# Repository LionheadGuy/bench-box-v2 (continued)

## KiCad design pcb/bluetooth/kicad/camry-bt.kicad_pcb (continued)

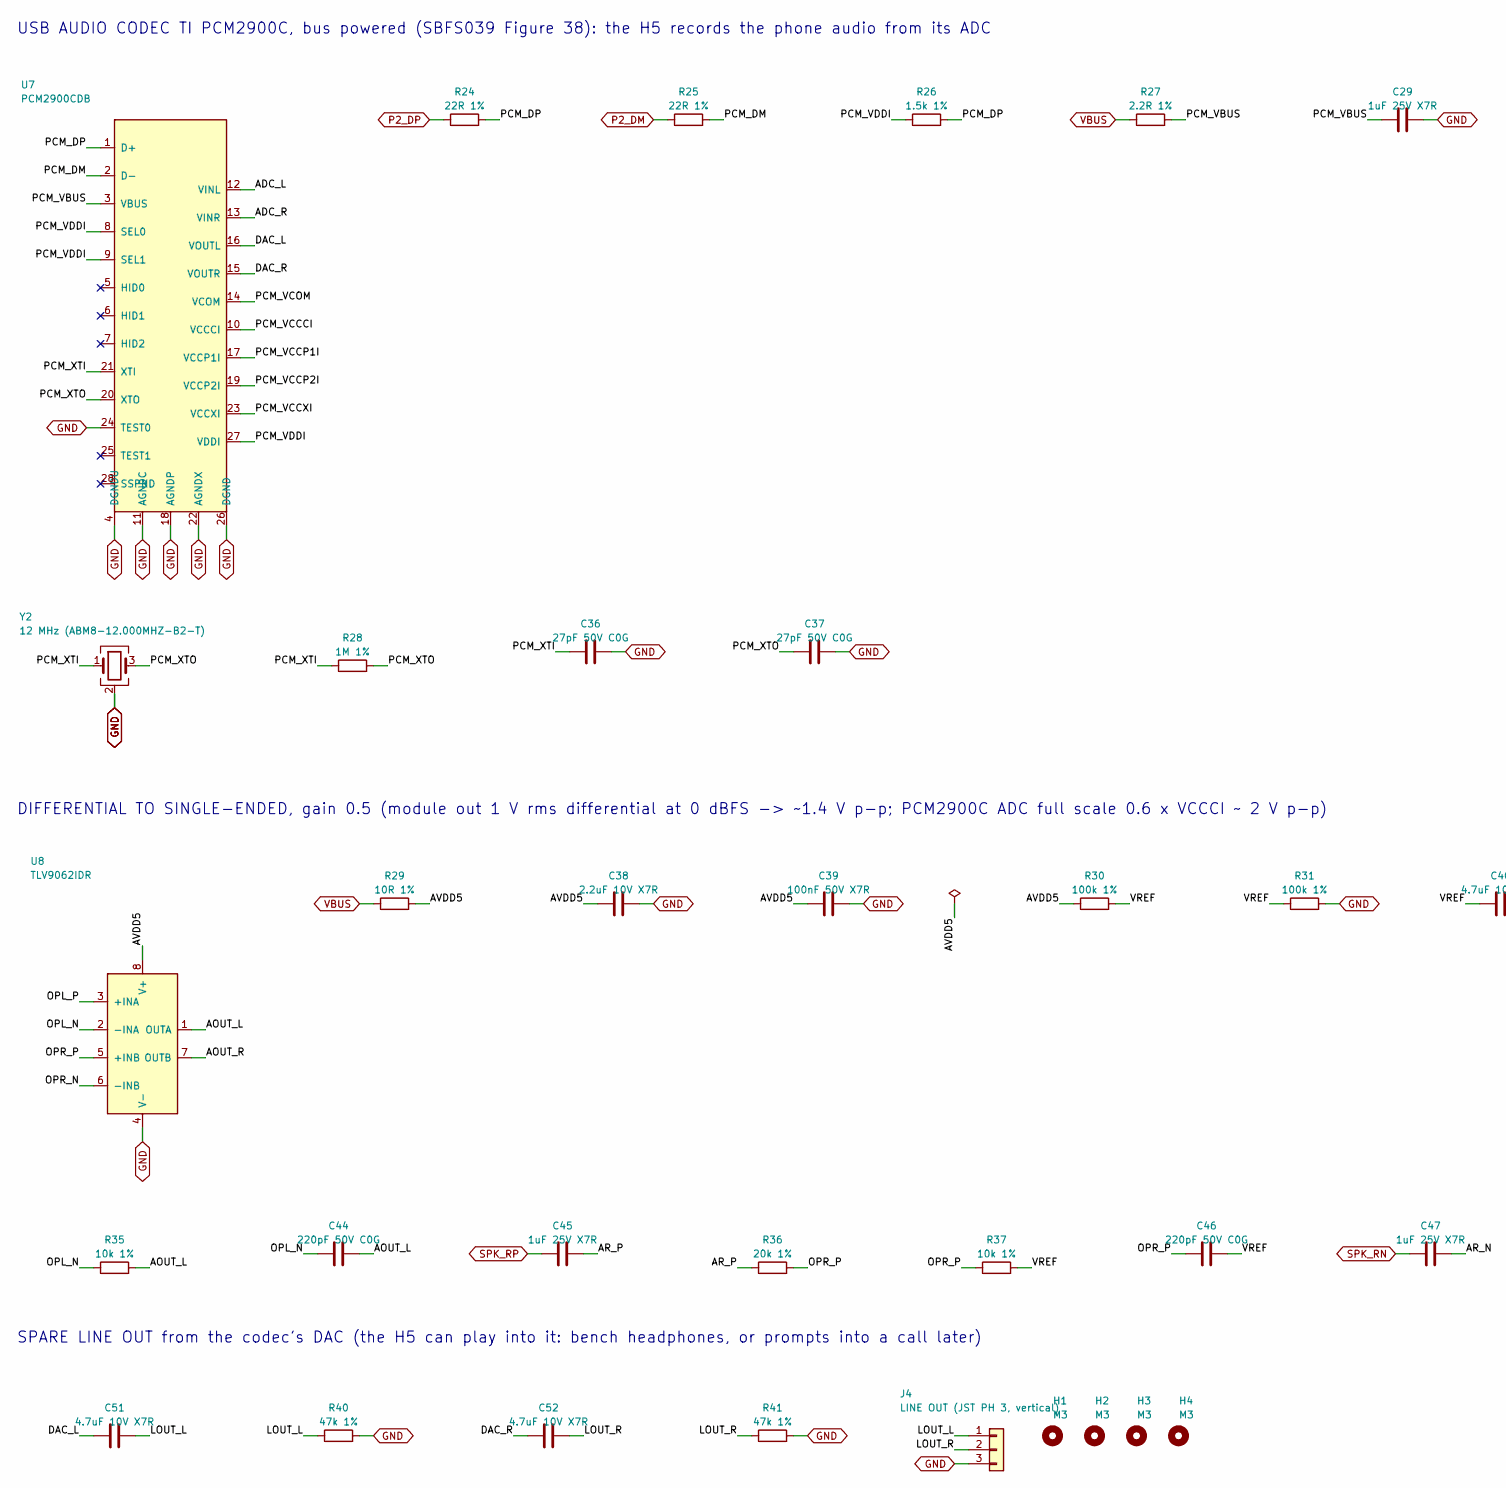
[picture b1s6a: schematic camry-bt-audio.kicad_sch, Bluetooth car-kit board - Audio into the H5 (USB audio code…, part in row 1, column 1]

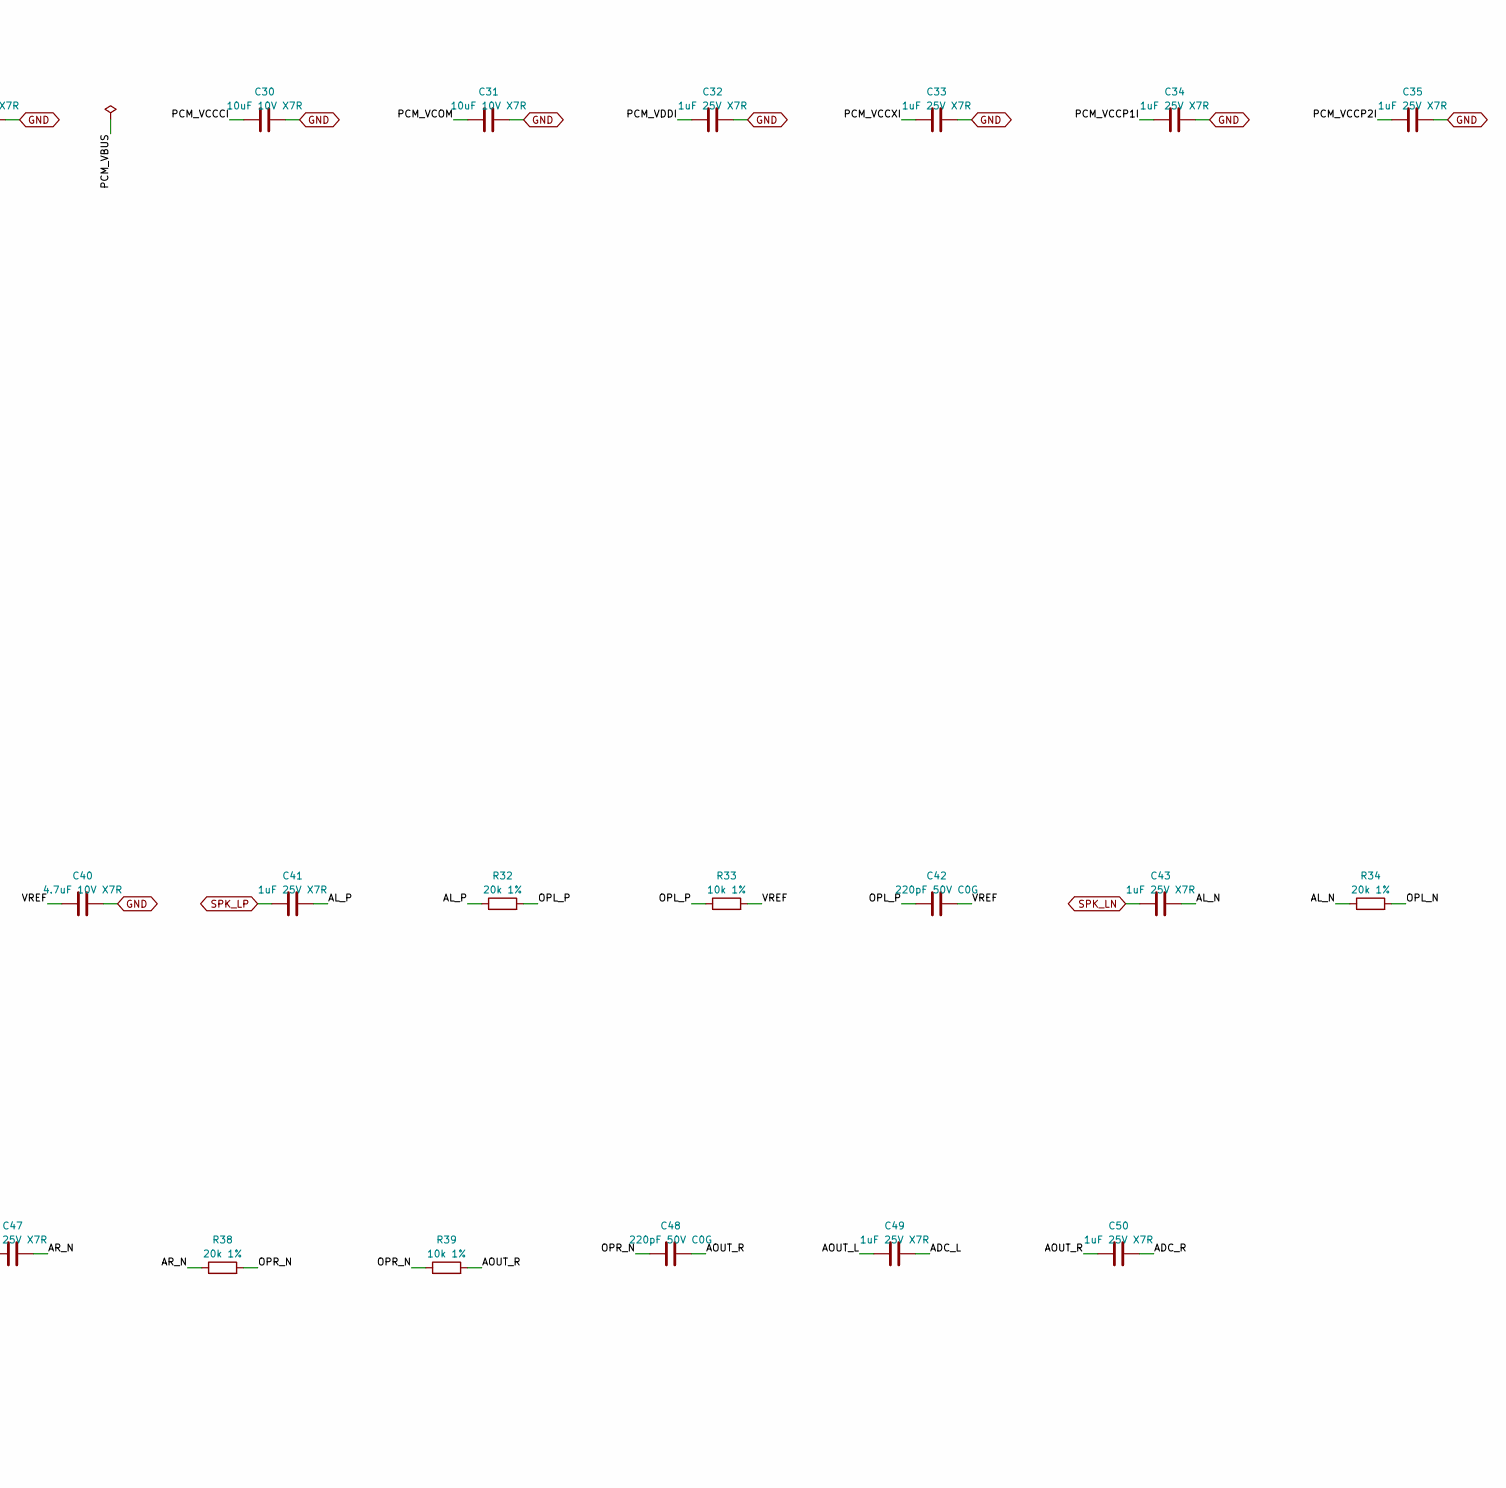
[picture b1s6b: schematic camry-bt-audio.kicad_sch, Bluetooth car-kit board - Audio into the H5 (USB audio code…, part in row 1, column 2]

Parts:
C29, C32, C33, C34, C35, C41, C43, C45, C47, C49, C50: 1uF 25V X7R; C_0603_1608Metric; MPN GRM188R71E105KA12D
C30, C31: 10uF 10V X7R; C_0805_2012Metric; MPN GRM21BR71A106KA73L
C36, C37: 27pF 50V C0G; C_0603_1608Metric; MPN GRM1885C1H270JA01D
C38: 2.2uF 10V X7R; C_0603_1608Metric; MPN GRM188R71A225KE15D
C39: 100nF 50V X7R; C_0603_1608Metric; MPN GRM188R71H104KA93D
C40, C51, C52: 4.7uF 10V X7R; C_0805_2012Metric; MPN GRM21BR71A475KA73L
C42, C44, C46, C48: 220pF 50V C0G; C_0603_1608Metric; MPN GRM1885C1H221JA01D
H1, H2, H3, H4: M3; MountingHole_3.2mm_M3
J4: LINE OUT (JST PH 3, vertical); JST_PH_B3B-PH-K_1x03_P2.00mm_Vertical; MPN B3B-PH-K-S(LF)(SN)
R24, R25: 22R 1%; R_0402_1005Metric; MPN RC0402FR-0722RL
R26: 1.5k 1%; R_0402_1005Metric; MPN RC0402FR-071K5L
R27: 2.2R 1%; R_0402_1005Metric; MPN RC0402FR-072R2L
R28: 1M 1%; R_0402_1005Metric; MPN RC0402FR-071ML
R29: 10R 1%; R_0402_1005Metric; MPN RC0402FR-0710RL
R30, R31: 100k 1%; R_0402_1005Metric; MPN RC0402FR-07100KL
R32, R34, R36, R38: 20k 1%; R_0402_1005Metric; MPN RC0402FR-0720KL
R33, R35, R37, R39: 10k 1%; R_0402_1005Metric; MPN RC0402FR-0710KL
R40, R41: 47k 1%; R_0402_1005Metric; MPN RC0402FR-0747KL
U7: PCM2900CDB; SSOP-28_5.3x10.2mm_P0.65mm; MPN PCM2900CDB
U8: TLV9062IDR; SOIC-8_3.9x4.9mm_P1.27mm; MPN TLV9062IDR
Y2: 12 MHz (ABM8-12.000MHZ-B2-T); Crystal_SMD_3225-4Pin_3.2x2.5mm; MPN ABM8-12.000MHZ-B2-T

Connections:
/Audio into the H5 (USB audio codec)/ADC_L: C49.2, U7.12 (VINL)
/Audio into the H5 (USB audio codec)/ADC_R: C50.2, U7.13 (VINR)
/Audio into the H5 (USB audio codec)/AL_N: C43.2, R34.1
/Audio into the H5 (USB audio codec)/AL_P: C41.2, R32.1
/Audio into the H5 (USB audio codec)/AOUT_L: C44.2, C49.1, R35.2, U8.1 (OUTA)
/Audio into the H5 (USB audio codec)/AOUT_R: C48.2, C50.1, R39.2, U8.7 (OUTB)
/Audio into the H5 (USB audio codec)/AR_N: C47.2, R38.1
/Audio into the H5 (USB audio codec)/AR_P: C45.2, R36.1
/Audio into the H5 (USB audio codec)/AVDD5: C38.1, C39.1, R29.2, R30.1, U8.8 (V+)
/Audio into the H5 (USB audio codec)/DAC_L: C51.1, U7.16 (VOUTL)
/Audio into the H5 (USB audio codec)/DAC_R: C52.1, U7.15 (VOUTR)
/Audio into the H5 (USB audio codec)/LOUT_L: C51.2, J4.1, R40.1
/Audio into the H5 (USB audio codec)/LOUT_R: C52.2, J4.2, R41.1
/Audio into the H5 (USB audio codec)/OPL_N: C44.1, R34.2, R35.1, U8.2 (-INA)
/Audio into the H5 (USB audio codec)/OPL_P: C42.1, R32.2, R33.1, U8.3 (+INA)
/Audio into the H5 (USB audio codec)/OPR_N: C48.1, R38.2, R39.1, U8.6 (-INB)
/Audio into the H5 (USB audio codec)/OPR_P: C46.1, R36.2, R37.1, U8.5 (+INB)
/Audio into the H5 (USB audio codec)/PCM_DM: R25.2, U7.2 (D-)
/Audio into the H5 (USB audio codec)/PCM_DP: R24.2, R26.2, U7.1 (D+)
/Audio into the H5 (USB audio codec)/PCM_VBUS: C29.1, R27.2, U7.3 (VBUS)
/Audio into the H5 (USB audio codec)/PCM_VCCCI: C30.1, U7.10 (VCCCI)
/Audio into the H5 (USB audio codec)/PCM_VCCP1I: C34.1, U7.17 (VCCP1I)
/Audio into the H5 (USB audio codec)/PCM_VCCP2I: C35.1, U7.19 (VCCP2I)
/Audio into the H5 (USB audio codec)/PCM_VCCXI: C33.1, U7.23 (VCCXI)
/Audio into the H5 (USB audio codec)/PCM_VCOM: C31.1, U7.14 (VCOM)
/Audio into the H5 (USB audio codec)/PCM_VDDI: C32.1, R26.1, U7.8 (SEL0), U7.9 (SEL1), U7.27 (VDDI)
/Audio into the H5 (USB audio codec)/PCM_XTI: C36.1, R28.1, U7.21 (XTI), Y2.1
/Audio into the H5 (USB audio codec)/PCM_XTO: C37.1, R28.2, U7.20 (XTO), Y2.3
/Audio into the H5 (USB audio codec)/VREF: C40.1, C42.2, C46.2, R30.2, R31.1, R33.2, R37.2
GND: C29.2, C30.2, C31.2, C32.2, C33.2, C34.2, C35.2, C36.2, C37.2, C38.2, C39.2, C40.2, J4.3, R31.2, R40.2, R41.2, U7.4 (DGNDU), U7.11 (AGNDC), U7.18 (AGNDP), U7.22 (AGNDX), U7.24 (TEST0), U7.26 (DGND), U8.4 (V-), Y2.2 (G), Y2.4 (G); also elsewhere on the board
P2_DM: R25.1; also elsewhere on the board
P2_DP: R24.1; also elsewhere on the board
SPK_LN: C43.1; also elsewhere on the board
SPK_LP: C41.1; also elsewhere on the board
SPK_RN: C47.1; also elsewhere on the board
SPK_RP: C45.1; also elsewhere on the board
VBUS: R27.1, R29.1; also elsewhere on the board

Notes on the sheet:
USB AUDIO CODEC TI PCM2900C, bus powered (SBFS039 Figure 38): the H5 records the phone audio from its ADC
DIFFERENTIAL TO SINGLE-ENDED, gain 0.5 (module out 1 V rms differential at 0 dBFS -> ~1.4 V p-p; PCM2900C ADC full scale 0.6 x VCCCI ~ 2 V p-p)
SPARE LINE OUT from the codec's DAC (the H5 can play into it: bench headphones, or prompts into a call later)

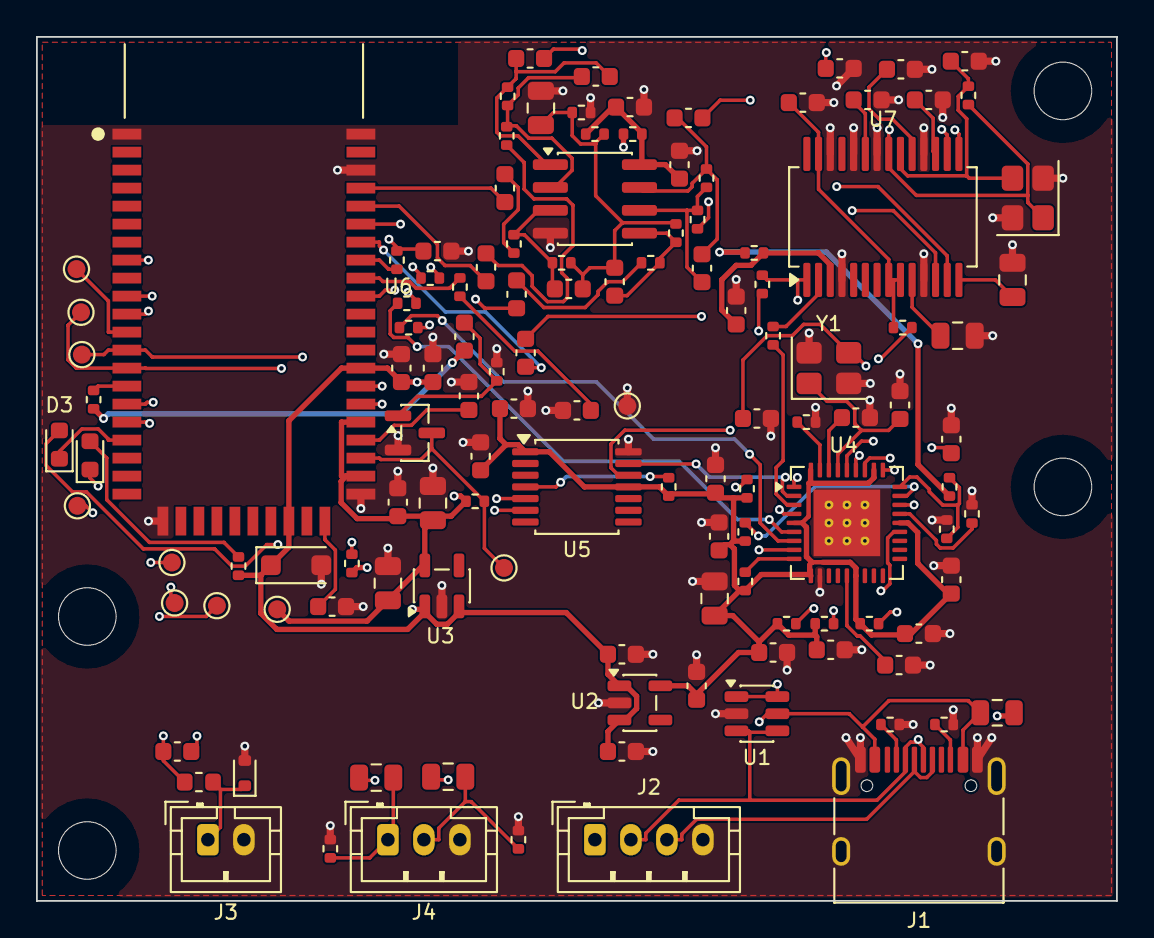
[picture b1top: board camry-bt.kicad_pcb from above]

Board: 4 copper layers, 60.0 x 48.0 mm, 128 parts (0 on the bottom side), 87 nets.

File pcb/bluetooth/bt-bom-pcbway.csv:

Item,Qty,Designators,Manufacturer,MPN,LCSC,Description,Footprint,Type,Substitute
1,1,U1,STMicroelectronics,USBLC6-2SC6,,"USB ESD protection, SOT-23-6",SOT-23-6,SMD,exact part only
2,2,U2 U3,Texas Instruments,TLV75533PDBVR,,"LDO 3.3 V 500 mA, SOT-23-5",SOT-23-5,SMD,exact part only
3,1,U4,Microchip,USB2514BI-AEZG,,"USB 2.0 4-port hub, QFN-36 6x6, -40 to 85 C",QFN-36-1EP_6x6mm_P0.5mm_EP3.7x3.7mm_ThermalVias,SMD,exact part only
4,1,U5,Microchip,MCP2221A-I/ST,,"USB to UART/I2C, TSSOP-14",TSSOP-14_4.4x5mm_P0.65mm,SMD,exact part only
5,1,U6,Feasycom,FSC-BT1026C,,"Bluetooth 5.1 audio module QCC3024, 52-pad stamp 13 x 26.9 mm (DigiKey stocks it)",Feasycom_FSC-BT1026x,SMD,exact part only
6,1,U7,Texas Instruments,PCM2900CDB,,"USB stereo audio codec, SSOP-28",SSOP-28_5.3x10.2mm_P0.65mm,SMD,exact part only
7,1,U8,Texas Instruments,TLV9062IDR,,"dual RRIO op amp 1.8-5.5 V, SOIC-8",SOIC-8_3.9x4.9mm_P1.27mm,SMD,exact part only
8,1,Q1,onsemi,2N7002LT1G,,"N-MOSFET 60 V 115 mA, SOT-23",SOT-23,SMD,exact part only
9,1,L1,Murata,LQG18HN15NJ00D,,"inductor 15 nH, 0603",L_0603_1608Metric,SMD,exact part only
10,1,D1,Littelfuse,SMF5.0A,,"TVS 5 V standoff, SOD-123FL",D_SOD-123F,SMD,exact part only
11,1,D2,Lite-On,LTST-C191TBKT,,"LED blue, 0603",LED_0603_1608Metric,SMD,exact part only
12,1,D3,Lite-On,LTST-C191KGKT,,"LED green, 0603",LED_0603_1608Metric,SMD,exact part only
13,1,D4,onsemi,ESD5Z5.0T1G,,"ESD diode 5 V, SOD-523",D_SOD-523,SMD,exact part only
14,1,Y1,Abracon,ABM8-24.000MHZ-B2-T,,"crystal 24 MHz, 18 pF, 3.2 x 2.5 mm",Crystal_SMD_3225-4Pin_3.2x2.5mm,SMD,exact part only
15,1,Y2,Abracon,ABM8-12.000MHZ-B2-T,,"crystal 12 MHz, 18 pF, 3.2 x 2.5 mm",Crystal_SMD_3225-4Pin_3.2x2.5mm,SMD,exact part only
16,1,F1,Bourns,MF-PSMF050X-2,,"PTC resettable fuse 0.5 A hold, 0805",Fuse_0805_2012Metric,SMD,exact part only
17,1,J1,Korean Hroparts Elec (HRO),TYPE-C-31-M-12,C165948,USB-C receptacle 16P,USB_C_Receptacle_HRO_TYPE-C-31-M-12,SMD,exact part only
18,1,J2,JST,B4B-PH-K-S(LF)(SN),,JST PH 4-pin vertical header,JST_PH_B4B-PH-K_1x04_P2.00mm_Vertical,THT,exact part only
19,1,J3,JST,B2B-PH-K-S(LF)(SN),,JST PH 2-pin vertical header,JST_PH_B2B-PH-K_1x02_P2.00mm_Vertical,THT,exact part only
20,1,J4,JST,B3B-PH-K-S(LF)(SN),,JST PH 3-pin vertical header,JST_PH_B3B-PH-K_1x03_P2.00mm_Vertical,THT,exact part only
21,3,C1 C23 C38,Murata,GRM188R71A225KE15D,,2.2 uF 10 V X7R 0603,C_0603_1608Metric,SMD,equivalent OK
22,4,C15 C16 C36 C37,Murata,GRM1885C1H270JA01D,,27 pF 50 V C0G 0603,C_0603_1608Metric,SMD,equivalent OK
23,1,C19,Murata,GRM188R71C474KA88D,,470 nF 16 V X7R 0603,C_0603_1608Metric,SMD,equivalent OK
24,18,C2 C3 C4 C17 C22 C24 C25 C29 C32 C33 C34 C35 C41 C43 C45 C47 C49 C50,Murata,GRM188R71E105KA12D,,1 uF 25 V X7R 0603,C_0603_1608Metric,SMD,equivalent OK
25,1,C26,Murata,GRM1885C1H150JA01D,,15 pF 50 V C0G 0603,C_0603_1608Metric,SMD,equivalent OK
26,2,C30 C31,Murata,GRM21BR71A106KA73L,,10 uF 10 V X7R 0805,C_0805_2012Metric,SMD,equivalent OK
27,4,C42 C44 C46 C48,Murata,GRM1885C1H221JA01D,,220 pF 50 V C0G 0603,C_0603_1608Metric,SMD,equivalent OK
28,6,C5 C12 C21 C40 C51 C52,Murata,GRM21BR71A475KA73L,,4.7 uF 10 V X7R 0805,C_0805_2012Metric,SMD,equivalent OK
29,13,C6 C7 C8 C9 C10 C11 C13 C14 C18 C20 C27 C28 C39,Murata,GRM188R71H104KA93D,,100 nF 50 V X7R 0603,C_0603_1608Metric,SMD,equivalent OK
30,2,R1 R2,Yageo,RC0402FR-075K1L,,5.1 k 1 % 0402,R_0402_1005Metric,SMD,equivalent OK
31,4,R14 R15 R24 R25,Yageo,RC0402FR-0722RL,,22 Ohm 1 % 0402,R_0402_1005Metric,SMD,equivalent OK
32,1,R18,Yageo,RC0402FR-072KL,,2 k 1 % 0402,R_0402_1005Metric,SMD,equivalent OK
33,4,R19 R20 R22 R23,Yageo,RC0402FR-071KL,,1 k 1 % 0402,R_0402_1005Metric,SMD,equivalent OK
34,1,R21,Yageo,RC0402FR-072K2L,,2.2 k 1 % 0402,R_0402_1005Metric,SMD,equivalent OK
35,1,R26,Yageo,RC0402FR-071K5L,,1.5 k 1 % 0402,R_0402_1005Metric,SMD,equivalent OK
36,1,R27,Yageo,RC0402FR-072R2L,,2.2 Ohm 1 % 0402,R_0402_1005Metric,SMD,equivalent OK
37,1,R28,Yageo,RC0402FR-071ML,,1 M 1 % 0402,R_0402_1005Metric,SMD,equivalent OK
38,1,R29,Yageo,RC0402FR-0710RL,,10 Ohm 1 % 0402,R_0402_1005Metric,SMD,equivalent OK
39,1,R3,Yageo,RC0402FR-0712KL,,12.0 k 1 % 0402,R_0402_1005Metric,SMD,equivalent OK
40,4,R32 R34 R36 R38,Yageo,RC0402FR-0720KL,,20 k 1 % 0402,R_0402_1005Metric,SMD,equivalent OK
41,11,R4 R7 R8 R11 R12 R13 R16 R33 R35 R37 R39,Yageo,RC0402FR-0710KL,,10 k 1 % 0402,R_0402_1005Metric,SMD,equivalent OK
42,2,R40 R41,Yageo,RC0402FR-0747KL,,47 k 1 % 0402,R_0402_1005Metric,SMD,equivalent OK
43,7,R5 R6 R9 R10 R17 R30 R31,Yageo,RC0402FR-07100KL,,100 k 1 % 0402,R_0402_1005Metric,SMD,equivalent OK

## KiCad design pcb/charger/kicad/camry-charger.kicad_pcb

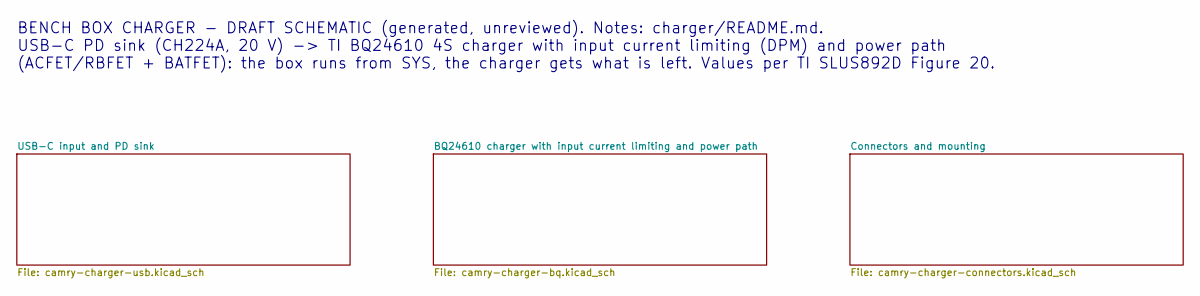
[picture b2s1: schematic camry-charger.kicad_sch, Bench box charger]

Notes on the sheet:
BENCH BOX CHARGER - DRAFT SCHEMATIC (generated, unreviewed). Notes: charger/README.md. USB-C PD sink (CH224A, 20 V) -> TI BQ24610 4S charger with input current limiting (DPM) and power path (ACFET/RBFET + BATFET): the box runs from SYS, the charger gets what is left. Values per TI SLUS892D Figure 2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

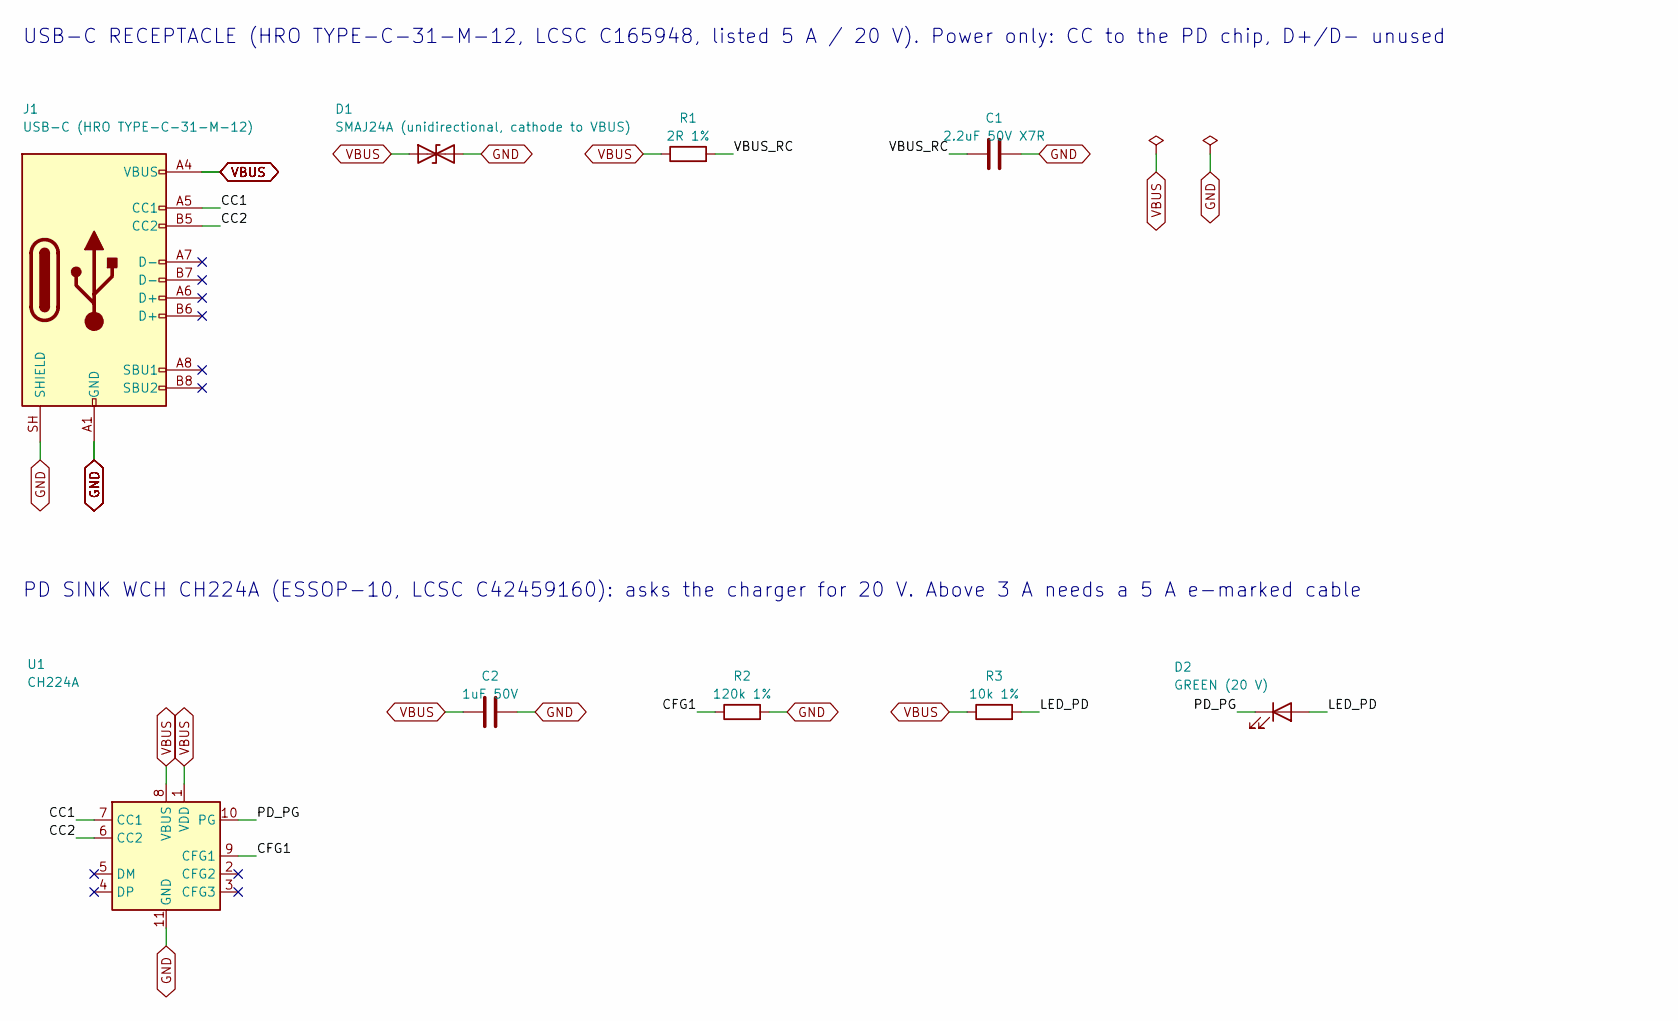
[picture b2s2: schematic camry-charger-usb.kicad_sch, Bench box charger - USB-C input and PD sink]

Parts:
C1: 2.2uF 50V X7R; C_1210_3225Metric; MPN C3225X7R1H225K250AB
C2: 1uF 50V; C_0805_2012Metric; MPN GRM21BR71H105KA12L
D1: SMAJ24A (unidirectional, cathode to VBUS); D_SMA; MPN SMAJ24A
D2: GREEN (20 V); LED_0603_1608Metric; MPN LTST-C191KGKT
J1: USB-C (HRO TYPE-C-31-M-12); USB_C_Receptacle_HRO_TYPE-C-31-M-12; MPN TYPE-C-31-M-12; LCSC C165948
R1: 2R 1%; R_2010_5025Metric; MPN RC2010FK-072RL
R2: 120k 1%; R_0603_1608Metric; MPN RC0603FR-07120KL
R3: 10k 1%; R_0603_1608Metric; MPN RC0603FR-0710KL
U1: CH224A; SSOP-10-1EP_3.9x4.9mm_P1mm_EP2.1x3.3mm; MPN CH224A; LCSC C42459160

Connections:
/USB-C input and PD sink/CC1: J1.A5 (CC1), U1.7 (CC1)
/USB-C input and PD sink/CC2: J1.B5 (CC2), U1.6 (CC2)
/USB-C input and PD sink/CFG1: R2.1, U1.9 (CFG1)
/USB-C input and PD sink/LED_PD: D2.2 (A), R3.2
/USB-C input and PD sink/PD_PG: D2.1 (K), U1.10 (PG)
/USB-C input and PD sink/VBUS_RC: C1.1, R1.2
GND: C1.2, C2.2, D1.2 (A2), J1.A1 (GND), J1.A12 (GND), J1.B1 (GND), J1.B12 (GND), J1.SH (SHIELD), R2.2, U1.11 (GND); also elsewhere on the board
VBUS: C2.1, D1.1 (A1), J1.A4 (VBUS), J1.A9 (VBUS), J1.B4 (VBUS), J1.B9 (VBUS), R1.1, R3.1, U1.1 (VDD), U1.8 (VBUS); also elsewhere on the board

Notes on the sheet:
USB-C RECEPTACLE (HRO TYPE-C-31-M-12, LCSC C165948, listed 5 A / 20 V). Power only: CC to the PD chip, D+/D- unused
PD SINK WCH CH224A (ESSOP-10, LCSC C42459160): asks the charger for 20 V. Above 3 A needs a 5 A e-marked cable
